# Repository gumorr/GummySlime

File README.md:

# GummySlime
A Cheesecake compatible SlimeVR tracker PCB.

# Overview
GummySlime is my own take on a Cheesecake PCB. The main features this has over regular Cheesecake PCBs are as follows:
- Designed to be (slightly) possible to solder by hand; this uses 0603 sized SMD components instead of 0402 equivalents. (Emphasis on **slightly**. You MUST be comfortable with SMD soldering.)
- Use of BMI compatible module PCBs instead of soldering the IMU directly on the board itself.
- Use of the ESP32 MCU instead of now outdated ESP12F modules.
- Exposed pads for adding auxilary modules.

# Building
**When you order PCBs, remember to change the PCB thickness to 1mm!**  
Most basic guidelines when building Cheesecake PCBs apply here; the general process is mostly the same. The one "gotcha" you should keep note of while
building is the USB-C connector: you should solder it on **BEFORE** soldering the ESP32 module. It is by far the most difficult component to solder on
to the PCB.

# BOM
| Component | Value  | Quantity |
| --------- | ------ | -------- |
| C1 | [10uF](https://www.digikey.com/en/products/detail/samsung-electro-mechanics/CL10B106MQ8NRNC/3887606) | 1 |
| C2,C3 | [1uF](https://www.digikey.com/en/products/detail/samsung-electro-mechanics/CL10B105KP8NNNC/3887604) | 2 |
| C4 | [0.1uF](https://www.digikey.com/en/products/detail/yageo/CC0603KRX7R7BB104/302822) | 1 |
| CN1 | [USB-C Connector](https://www.digikey.com/en/products/detail/gct/USB4105-GF-A/11198441) | 1 |
| D1 | [Red LED](https://www.digikey.com/en/products/detail/dialight/5973005507F/9385429) | 1 |
| D2 | [Green LED](https://www.digikey.com/en/products/detail/dialight/5973324507F/9385437) | 1 |
| D3 | [1N5819W](https://www.digikey.com/en/products/detail/smc-diode-solutions/1N5819W/15964237) | 1 |
| Q1 | [IRLML6401](https://www.digikey.com/en/products/detail/infineon-technologies/IRLML6401TRPBF/811442) | 1 |
| R1,R2 | [5.1K](https://www.digikey.com/en/products/detail/vishay-dale/RCS06035K10FKEA/5868559) | 2 |
| R3 | [3K](https://www.digikey.com/en/products/detail/vishay-dale/RCS06033K00FKEA/5868535) | 1 |
| R4,R5 | [1K](https://www.digikey.com/en/products/detail/vishay-dale/RCS06031K00FKEA/5866934) | 2 |
| R6,R7 | [100K](https://www.digikey.com/en/products/detail/vishay-dale/RCS0603100KFKEA/5866946) | 2 |
| R8,R9 | [4.7K](https://www.digikey.com/en/products/detail/vishay-dale/RCS06034K70FKEA/5866938) | 2 |
| SW1 | [SSSS811101](https://www.digikey.com/en/products/detail/alps-alpine/SSSS811101/19529062) | 1 |
| U1 | [ESP32-C3-WROOM-02](https://www.digikey.com/en/products/detail/espressif-systems/ESP32-C3-WROOM-02-H4/14553033) | 1 |
| U2 | [IMU Module](https://store.kouno.xyz/products/lsm6dso-module) | 1 |
| U3 | [MIC5504-3.3Y](https://www.digikey.com/en/products/detail/microchip-technology/MIC5504-3-3YM5-TR/4864018) | 1 |
| U4 | [TP4057](https://www.digikey.com/en/products/detail/evvo/TP4057/22482076) | 1 |

# Flashing
You will most likely have to flash using VS Code. Here are all of the relevant settings I personally use for flashing these boards:

### platformio.ini
```
[env:esp32c3]
platform = espressif32 @ 6.7.0
platform_packages =
  framework-arduinoespressif32 @ https://github.com/espressif/arduino-esp32.git#3.0.1
  framework-arduinoespressif32-libs @ https://github.com/espressif/arduino-esp32/releases/download/3.0.1/esp32-arduino-libs-3.0.1.zip
build_flags =
  ${env.build_flags}
  -DESP32C3
  -DARDUINO_USB_MODE=1
  -DARDUINO_USB_CDC_ON_BOOT=1
board = lolin_c3_mini
upload_speed = 921600
```

### defines.h
```
#define IMU IMU_LSM6DSO
#define SECOND_IMU IMU
#define IMU_ROTATION DEG_270
#define SECOND_IMU_ROTATION DEG_270

#define PRIMARY_IMU_OPTIONAL false
#define SECONDARY_IMU_OPTIONAL true

#define BATTERY_MONITOR BAT_EXTERNAL

#define PIN_IMU_SDA 5
#define PIN_IMU_SCL 4
#define PIN_IMU_INT 6
#define PIN_IMU_INT_2 8
#define LED_PIN LED_OFF
//  #define LED_INVERTED false
#define PIN_BATTERY_LEVEL 3

#define BATTERY_SHIELD_RESISTANCE 0
#define BATTERY_SHIELD_R1 100
#define BATTERY_SHIELD_R2 100
```

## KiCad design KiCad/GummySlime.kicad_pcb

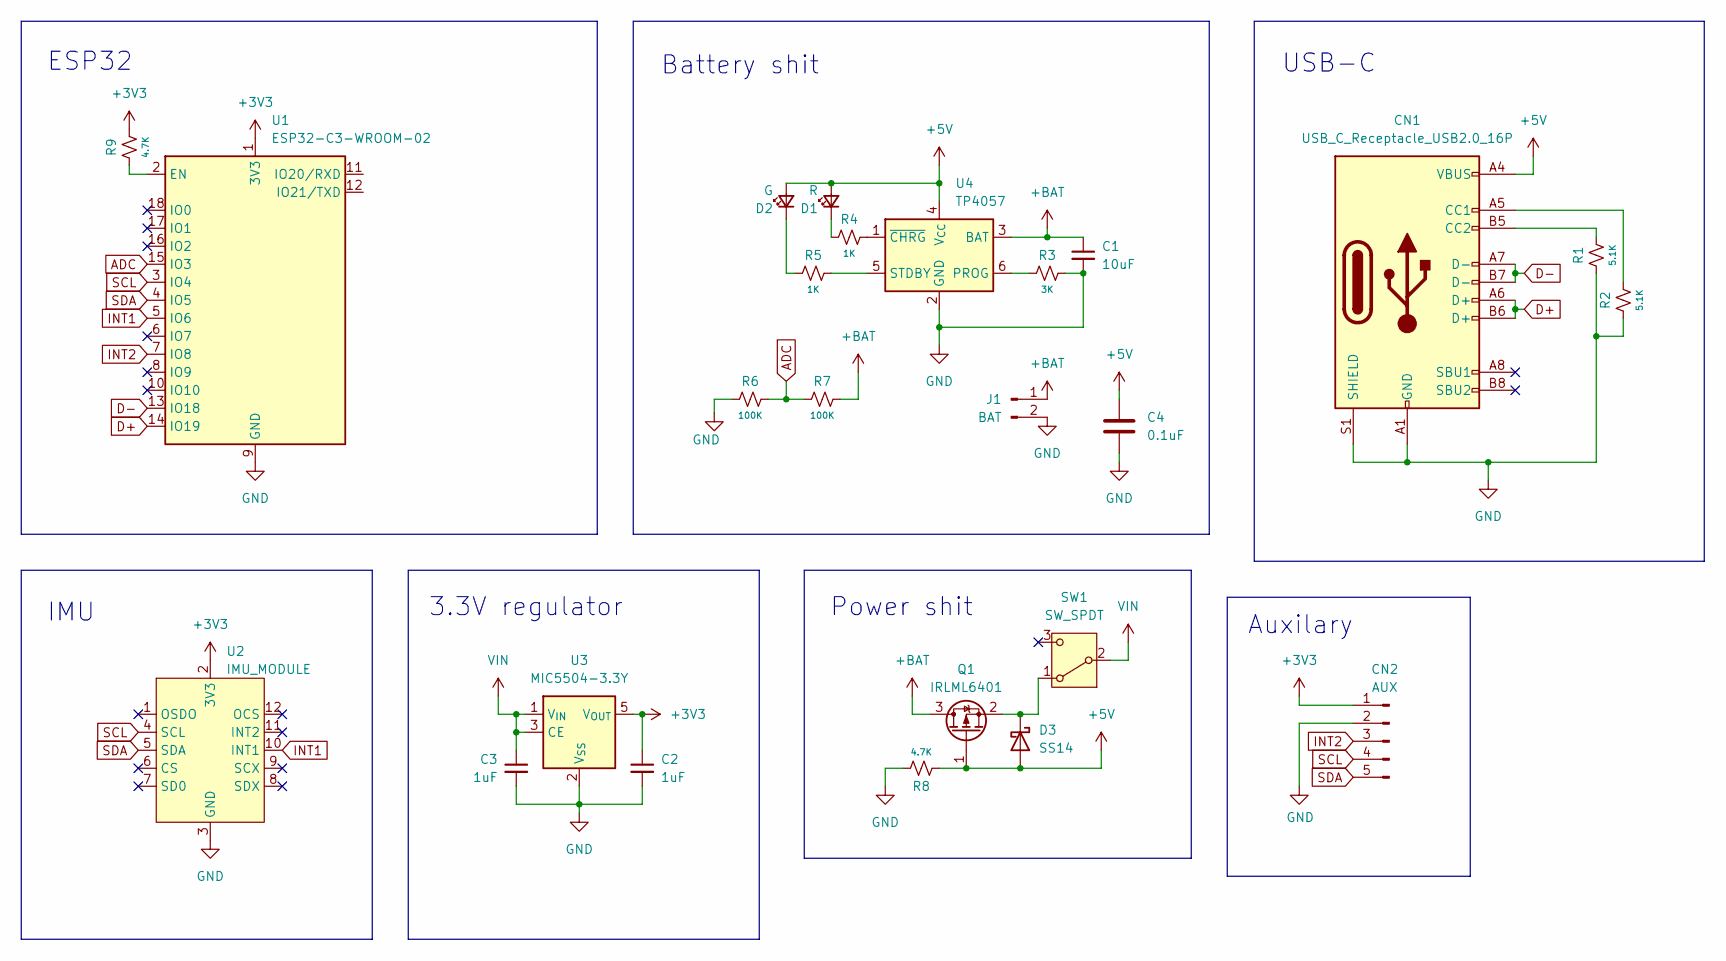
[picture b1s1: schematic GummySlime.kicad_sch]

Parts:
C1: 10uF; C_0603_1608Metric_Pad1.08x0.95mm_HandSolder
C2, C3: 1uF; C_0603_1608Metric_Pad1.08x0.95mm_HandSolder
C4: 0.1uF; C_0603_1608Metric_Pad1.08x0.95mm_HandSolder
CN1: USB_C_Receptacle_USB2.0_16P; USB_C_Receptacle_GCT_USB4105-xx-A_16P_TopMnt_Horizontal
CN2: AUX; AUX CONNECTOR
D1: R; LED_0603_1608Metric_Pad1.05x0.95mm_HandSolder
D2: G; LED_0603_1608Metric_Pad1.05x0.95mm_HandSolder
D3: SS14; D_SOD-123
J1: BAT; PinHeader_1x02_P2.54mm_Vertical
Q1: IRLML6401; SOT-23
R1, R2: 5.1K; R_0603_1608Metric_Pad0.98x0.95mm_HandSolder
R3: 3K; R_0603_1608Metric_Pad0.98x0.95mm_HandSolder
R4, R5: 1K; R_0603_1608Metric_Pad0.98x0.95mm_HandSolder
R6, R7: 100K; R_0603_1608Metric_Pad0.98x0.95mm_HandSolder
R8, R9: 4.7K; R_0603_1608Metric_Pad0.98x0.95mm_HandSolder
SW1: SW_SPDT; SW_SPDT_PCM12
U1: ESP32-C3-WROOM-02
U2: IMU_MODULE; BMI_LSM
U3: MIC5504-3.3Y; SOT-23-5_HandSoldering
U4: TP4057; TSOT-23-6

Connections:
+3V3: C2.1, CN2.1, R9.2, U1.1 (3V3), U2.2 (3V3), U3.5 (V_{OUT})
+5V: C4.1, CN1.A4 (VBUS), CN1.A9 (VBUS), CN1.B4 (VBUS), CN1.B9 (VBUS), D1.2 (A), D2.2 (A), D3.2 (A), Q1.1 (G), R8.1, U4.4 (V_{CC})
+BAT: C1.1, J1.1, Q1.3 (D), R7.2, U4.3 (BAT)
ADC: R6.2, R7.1, U1.15 (IO3)
D+: CN1.A6 (D+), CN1.B6 (D+), U1.14 (IO19)
D-: CN1.A7 (D-), CN1.B7 (D-), U1.13 (IO18)
GND: C1.2, C2.2, C3.2, C4.2, CN1.A1 (GND), CN1.A12 (GND), CN1.B1 (GND), CN1.B12 (GND), CN1.S1 (SHIELD), CN2.2, J1.2, R1.1, R2.1, R3.2, R6.1, R8.2, U1.9 (GND), U1.19 (GND), U2.3 (GND), U3.2 (V_{SS}), U4.2 (GND)
INT1: U1.5 (IO6), U2.10 (INT1)
INT2: CN2.3, U1.7 (IO8)
unnamed: CN1.A5 (CC1), R2.2
unnamed: CN1.B5 (CC2), R1.2
unnamed: D1.1 (K), R4.1
unnamed: D2.1 (K), R5.1
unnamed: D3.1 (K), Q1.2 (S), SW1.1 (A)
unnamed: R9.1, U1.2 (EN)
unnamed: R3.1, U4.6 (PROG)
unnamed: R5.2, U4.5 (STDBY)
unnamed: R4.2, U4.1 (~CHRG)
SCL: CN2.4, U1.3 (IO4), U2.4 (SCL)
SDA: CN2.5, U1.4 (IO5), U2.5 (SDA)
VIN: C3.1, SW1.2 (B), U3.1 (V_{IN}), U3.3 (CE)

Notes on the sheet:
Power shit
USB-C
3.3V regulator
Auxilary
ESP32
Battery shit
IMU

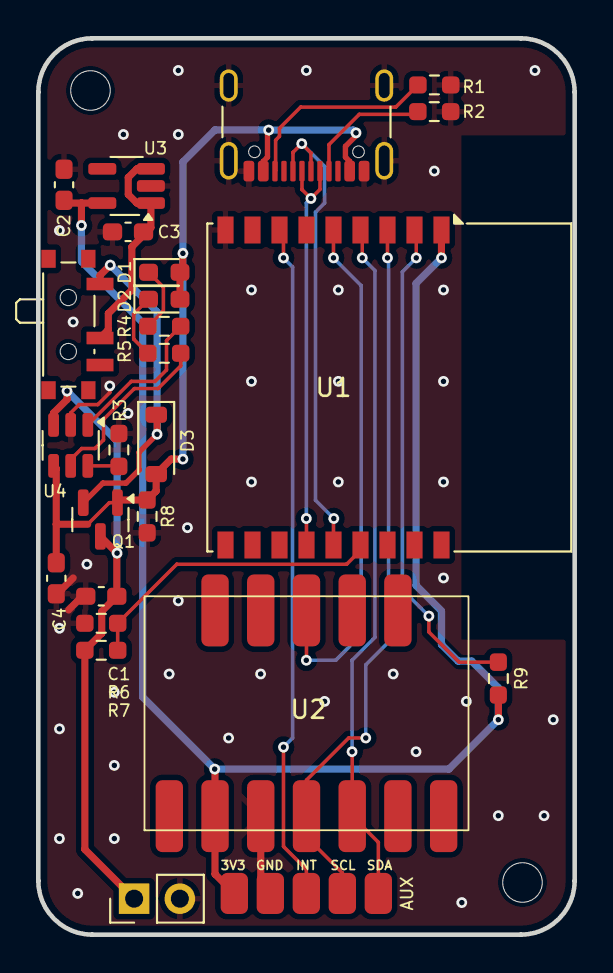
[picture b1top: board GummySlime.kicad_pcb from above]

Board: 2 copper layers, 29.8 x 49.8 mm, 25 parts (0 on the bottom side), 21 nets.

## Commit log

2024-12-03 whoops
2024-12-03 add readme
2024-12-04 adds digikey links to parts in readme BOM
